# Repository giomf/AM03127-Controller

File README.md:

# AM03127 LED Panel Controller

This project provides a controller for AM03127 LED panels using an ESP32-C3 microcontroller. It communicates with the panel via RS232 and exposes a REST API through an HTTP server, along with a web interface for easy control.

## Features

- Control AM03127 LED panels via RS232 communication
- Display text with various animations and effects
- Create and manage schedules for automated content display
- Set and display the panel's internal clock
- RESTful API for programmatic control
- Web interface for easy management and OTA updates

## Hardware Requirements

- ESP32-C3 microcontroller
- AM03127 LED panel
- RS232 interface between ESP32-C3 and LED panel

## PCB Design

A custom PCB has been designed for this project. All PCB-related files, including schematics, board layouts, and manufacturing files, can be found in the [PCB](PCB/) folder.

## Software Architecture

The project is built with Rust and uses the following components:

- **Embassy**: Async runtime for embedded systems
- **ESP-HAL**: Hardware abstraction layer for ESP32 devices
- **PicoServe**: Lightweight HTTP server for embedded systems
- **Heapless**: Collections that don't require dynamic memory allocation

## Programs

The repository is a Cargo workspace plus the firmware, which is built separately for the ESP32-C3.

| Directory | What it is |
|---|---|
| [`am03127-firmware`](am03127-firmware/) | Firmware for the ESP32-C3: drives the panel over RS232, stores pages and schedules in flash, serves the REST API and the web UI, accepts OTA updates. |
| [`am03127-webui`](am03127-webui/) | Web UI written in Rust with [Leptos](https://leptos.dev) (WebAssembly). Edit pages and schedules, sync the clock, upload firmware. |
| [`am03127-server`](am03127-server/) | Server that consolidates all panels into one web UI and forwards each panel's API. |
| [`am03127-cli`](am03127-cli/) | Command line tool to control several panels at once. |
| [`am03127-client`](am03127-client/) | Shared HTTP client for the panel API and the `panel-config.toml` parser. Used by the CLI, the web UI and the server. |
| [`am03127-commands`](am03127-commands/) | Shared `no_std` models (pages, schedules, clock) and their AM03127 command encoding. Used by the firmware and everything else. |

### Firmware

The firmware connects to Wi-Fi, restores the stored pages and schedules on the panel and serves the API on port 80. The Wi-Fi credentials are compiled in:

```sh
export WIFI_SSID="MyNetwork" WIFI_PASS="secret"
just webui-firmware                     # build the web UI the firmware embeds
cd am03127-firmware && cargo run --release   # flash over USB (also writes the partition table)
```

For updates over Wi-Fi, `just save-image` builds the web UI and the release firmware into `firmware.bin`, and `just ota <panel-ip>` uploads it. The web UI's Device tab can upload it as well.

`GET /status` reports the build and the controller's health, shown in the web UI and by `am03127-cli status`:

- `version`: short git hash of the build, `-dirty` if the tree had uncommitted changes
- `uptime_secs`, `rssi` (Wi-Fi dBm), `heap_free` / `heap_used` (bytes)
- `panel_ok`: whether the panel answered the last command (`null` before the first one)

### Web UI

One Leptos crate, built in two variants:

- **Device** (default): served by the firmware for the panel it runs on.
- **Server** (`--features server`): shows a bar with all panels and their status; click a panel to edit it.

Both share the same tables and Device tab. Pages and schedules are edited in place; the last row of each table adds a new entry.

### Server

`am03127-server` serves the server variant of the web UI and forwards `/api/panel/<name>/…` to the panel's API, so the browser only talks to the server and the panels need no CORS.

```sh
am03127-server --config panel-config.toml --listen 0.0.0.0:8080 --web-root <built web UI>
```

`GET /api/panels` lists the configured panels.

### CLI

`am03127-cli` works on all (non-hidden) panels of `panel-config.toml`, or on the ones given with `--panels`:

```sh
am03127-cli status                                   # reachability, firmware version and health of each panel
am03127-cli info firmware.bin                        # build info of a firmware file
am03127-cli clock                                    # set the clocks to the local time
am03127-cli page A "Hello" --leading scroll_left     # send page A
am03127-cli schedule A A --from 2026-12-24 --to 2026-12-26   # show page A in that window
am03127-cli update firmware.bin --panels Kitchen     # OTA update one panel
am03127-cli --help                                   # all commands and options
```

### Panel configuration

The CLI and the server read the panels from a `panel-config.toml`:

```toml
[[panels]]
name = "Kitchen"
address = "192.168.1.23"   # host name or IP of the panel
floor = "Obergeschoss"     # optional, groups the panels in the server's web UI
model = "long"             # optional: "long" or "color"; omit for a standard panel

[[panels]]
name = "Spare"
address = "LED-8E-84.lan"
hidden = true              # skipped unless named with --panels
```

## Nix

The flake provides:

- Packages: `am03127-cli` (default), `am03127-server`, `am03127-webui` (server variant, built).
- NixOS modules:
  - `am03127-server`: runs the server with the web UI (`configFile`, `address`, `port`, `openFirewall`).
  - `am03127-clock`: syncs the panel clocks on a systemd timer.
  - `am03127-wednesday-schedule`: programs a weekly schedule slot.
- A dev shell with the toolchain, Trunk, espflash and just.

```nix
services.am03127-server = {
  enable = true;
  configFile = ./panel-config.toml;
  port = 80;
  openFirewall = true;
};
```

## Development

| Recipe | What it does |
|---|---|
| `just webui` | Web UI (device variant) with live reload against a mock panel (`am03127-webui/mock.py`). |
| `just webui-server` | Web UI (server variant) with `am03127-server` and two mock panels. |
| `just webui-firmware` | Builds the gzipped web UI the firmware embeds. |
| `just save-image` | Builds web UI and release firmware into `firmware.bin`. |
| `just ota <ip>` | Uploads `firmware.bin` to a panel. |

Both web UI recipes serve on <http://127.0.0.1:8080/>.

## API Documentation

The REST API documentation is available as [OpenAPI Specification](docs/openapi.yaml)

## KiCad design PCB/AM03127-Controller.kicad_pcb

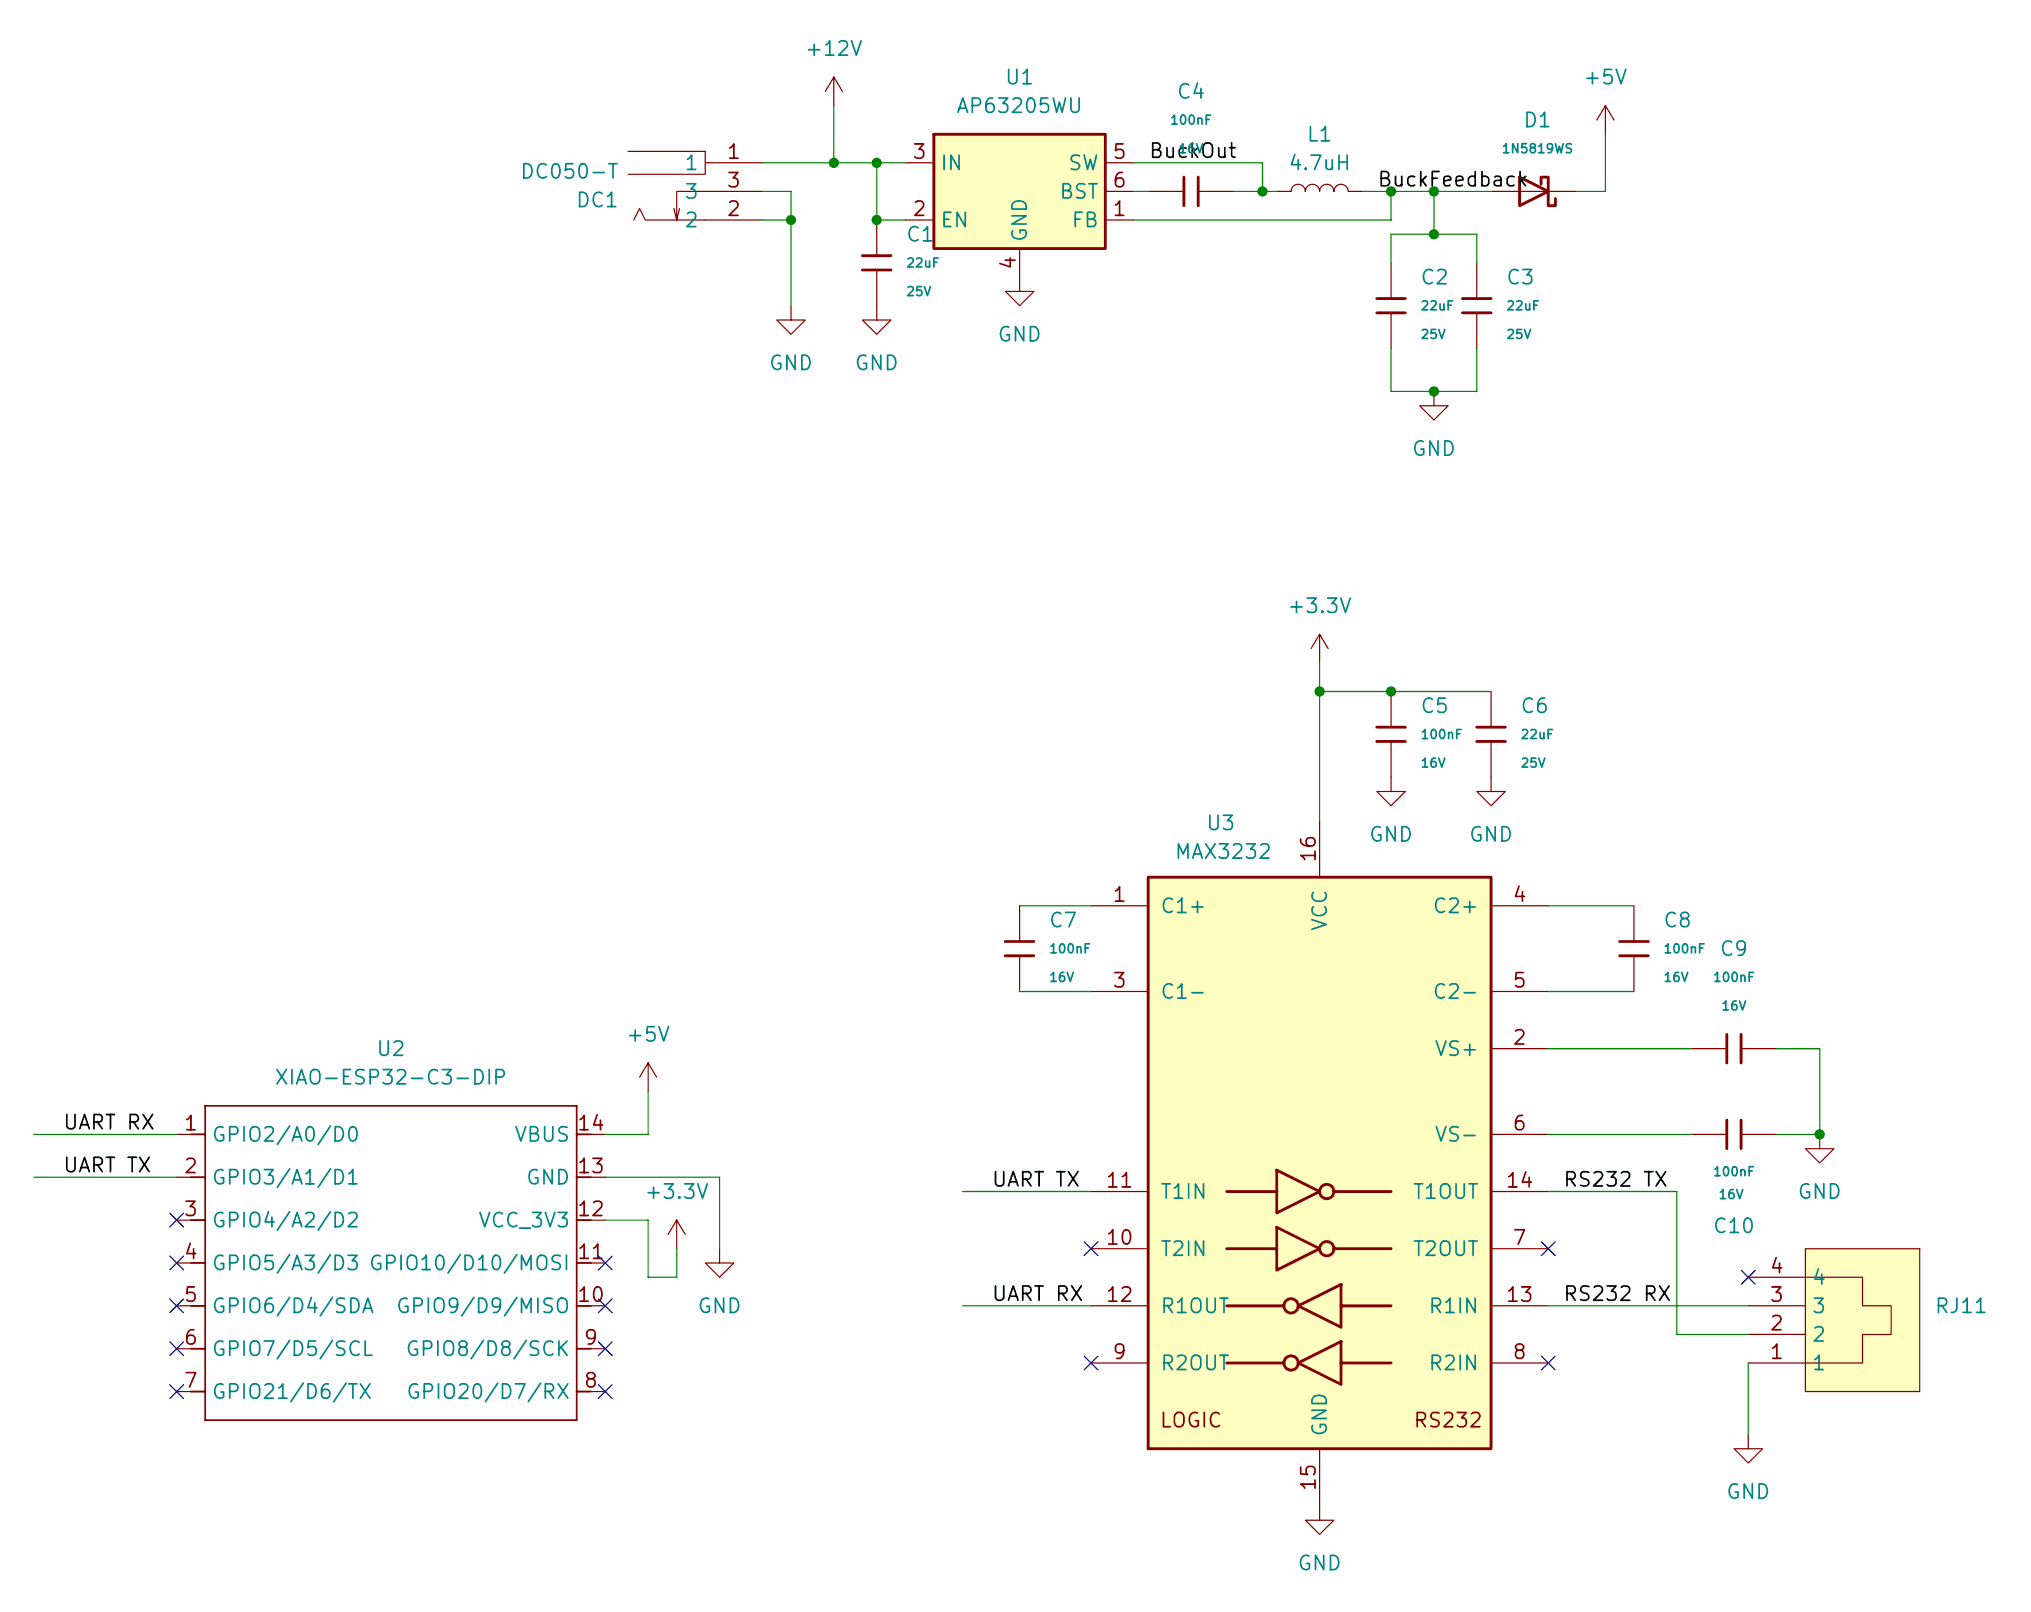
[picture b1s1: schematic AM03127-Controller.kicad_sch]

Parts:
C1, C2, C3, C6: 22uF; C_1206; Voltage Rated 25V; Tolerance ±10%; Part CL31A226KAHNNNE; LCSC C12891
C4, C5, C7, C8, C9, C10: 100nF; C_0402; Voltage Rated 16V; Tolerance ±10%; Part CL05B104KO5NNNC; LCSC C1525
D1: 1N5819WS; D_SOD-323; Forward Voltage (Vf@If) 600mV@1A; Reverse Voltage (Vr) 40V; Part 1N5819WS; LCSC C191023
DC1: DC050-T; DC-IN_DC050-T; LCSC Part C431534
L1: 4.7uH; L_1008_2520Metric
RJ11: PCB-6P4C-90_C189746; RJ11-TH_PCB-6P4C-90_C189746; LCSC Part C189746
U1: AP63205WU; TSOT-23-6
U2: XIAO-ESP32-C3-DIP; XIAO-ESP32C3-DIP
U3: MAX3232; SOIC-16_3.9x9.9mm_P1.27mm

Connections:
+3.3V: C5.1, C6.1, U2.12 (VCC_3V3), U3.16 (VCC)
+5V: D1.1, U2.14 (VBUS)
+12V: C1.1, DC1.1, U1.2 (EN), U1.3 (IN)
/BuckFeedback: C2.1, C3.1, D1.2, L1.2, U1.1 (FB)
/BuckOut: C4.2, L1.1, U1.5 (SW)
/RS232 RX: RJ11.3, U3.13 (R1IN)
/RS232 TX: RJ11.2, U3.14 (T1OUT)
/UART RX: U2.1 (GPIO2/A0/D0), U3.12 (R1OUT)
/UART TX: U2.2 (GPIO3/A1/D1), U3.11 (T1IN)
GND: C1.2, C2.2, C3.2, C5.2, C6.2, C9.2, C10.2, DC1.2, DC1.3, RJ11.1, U1.4 (GND), U2.13 (GND), U3.15 (GND)
unnamed: C4.1, U1.6 (BST)
unnamed: C7.1, U3.1 (C1+)
unnamed: C7.2, U3.3 (C1-)
unnamed: C8.1, U3.4 (C2+)
unnamed: C8.2, U3.5 (C2-)
unnamed: C9.1, U3.2 (VS+)
unnamed: C10.1, U3.6 (VS-)

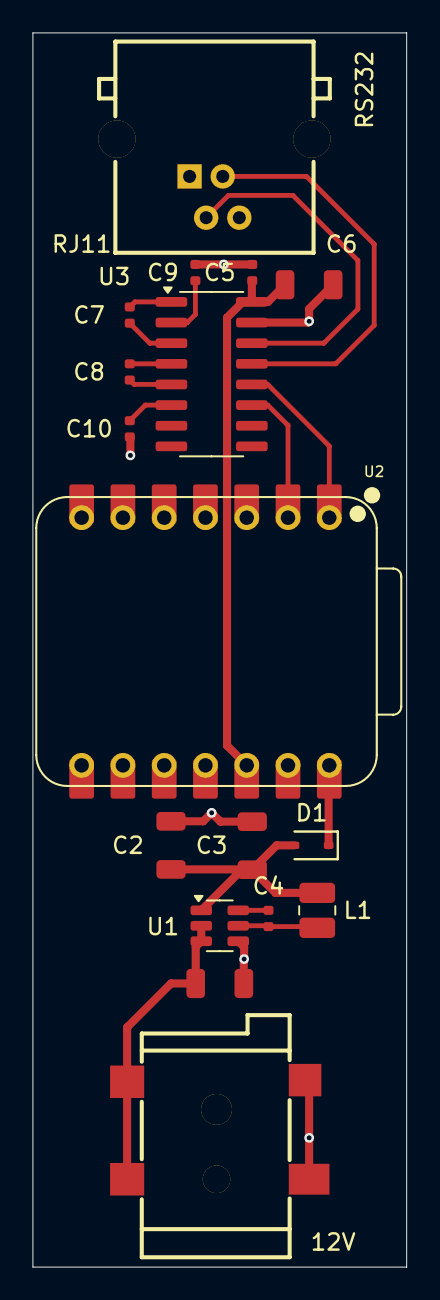
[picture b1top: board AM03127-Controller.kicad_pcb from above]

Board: 2 copper layers, 23.0 x 76.0 mm, 17 parts (0 on the bottom side), 17 nets.

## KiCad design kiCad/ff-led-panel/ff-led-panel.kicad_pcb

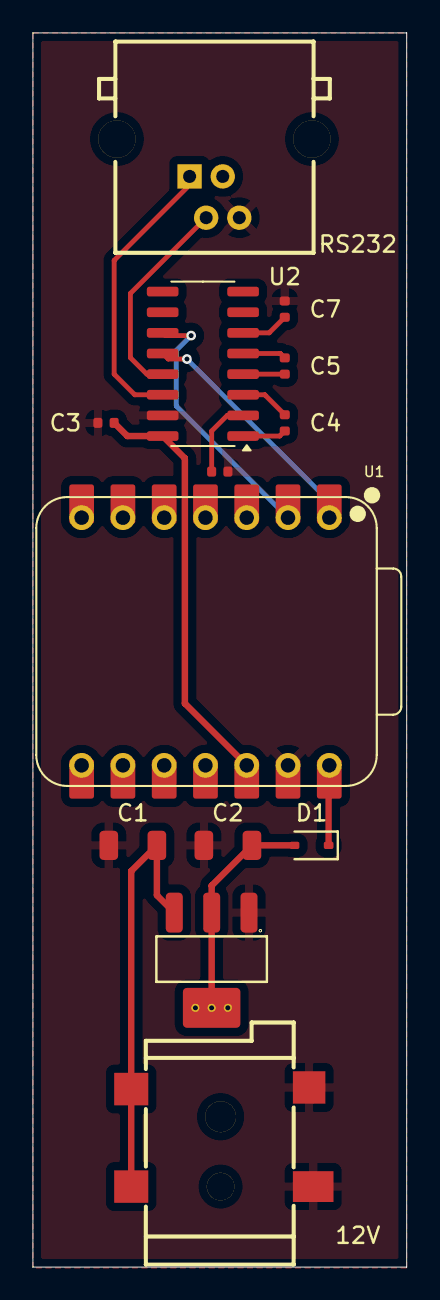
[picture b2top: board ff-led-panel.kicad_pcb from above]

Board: 2 copper layers, 23.0 x 76.0 mm, 13 parts (0 on the bottom side), 15 nets.

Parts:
12V: DC050-T; DC-IN_DC050-T
C1: 10uF; C_1206
C2: 22uF; C_1206
C3, C4, C5, C6, C7: 100nF; C_0402
D1: 1N5819WS; D_SOD-323
RS232: PCB-6P4C-90_C189746; RJ11-TH_PCB-6P4C-90_C189746
U1: XIAO-ESP32-C3-DIP; XIAO-ESP32C3-DIP
U2: MAX3232; SOIC-16_3.9x9.9mm_P1.27mm
U3: AMS1117; SOT-223_L6.5-W3.5-P2.30-LS7.0-BR

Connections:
/3.3V: C3.1, U1.12 (VCC_3V3), U2.16 (VCC)
/5V: C2.1, D1.2, U3.2 (VOUT), U3.4 (VOUT)
/5VD: D1.1, U1.14 (VBUS)
/12V: 12V.1, C1.1, U3.3 (VIN)
/RS232 RX: RS232.2, U2.13 (R1IN)
/RS232 TX: RS232.1, U2.14 (T1OUT)
/UART RX: U1.1 (GPIO2/A0/D0), U2.12 (R1OUT)
/UART TX: U1.2 (GPIO3/A1/D1), U2.11 (T1IN)
GND: 12V.2, 12V.3, C1.2, C2.2, C3.2, C6.2, C7.2, RS232.4, U1.13 (GND), U2.15 (GND), U3.1 (GND)
unnamed: C4.1, U2.1 (C1+)
unnamed: C4.2, U2.3 (C1-)
unnamed: C5.1, U2.4 (C2+)
unnamed: C5.2, U2.5 (C2-)
unnamed: C6.1, U2.2 (VS+)
unnamed: C7.1, U2.6 (VS-)

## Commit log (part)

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2025-03-31 init
2025-04-02 add picoserve hello world
2025-04-02 feat: Add AM03127 module with ID and command wrapping functions
2025-04-02 refactor: Replace format! with write! for no_std compatibility
2025-04-03 feat: Add page content module with display and formatting enums
2025-04-03 refactor: Convert page_content module to no_std with heapless::String
2025-04-03 feat: Add AM03127 module with page content and command wrapping functionality
2025-04-03 refactor: Add global string size constants and remove serde cfg flags
2025-04-03 refactor: Consolidate string size to single constant of 32
2025-04-03 feat: Add formatting module with Font, ColumnStart, and Clock enums
2025-04-03 style: Refactor formatting.rs to use core::fmt and consistent formatting
2025-04-03 Add am03127 library
2025-04-03 add uart
2025-04-08 Add webserver state
2025-04-13 Add uart write method
2025-04-13 Add clock endpoints
2025-04-13 Add text endpoint
2025-04-14 Add openapi documentation
2025-04-14 Add root endpoint servcing a static html
2025-04-14 Fix minor issues
2025-04-19 Add am03127 datasheat
2025-04-19 Init kicad project
2025-04-19 Add schedule endpoints
2025-04-20 Refactor AM03127 lib
2025-04-20 Add Schedule API
2025-04-20 Split server routes
2025-04-24 Add storage
2025-04-25 Add storage to server endpoints
2025-04-26 Add panel
2025-04-26 Add error handling
2025-04-28 Add schedule storage
2025-04-28 Add id validation for API endpoints
2025-04-28 Add pages GET endpoint
2025-04-28 Create own module for routers
2025-04-28 Add schedules GET endpoint
2025-04-28 Pass size for storage data buffer
2025-04-28 add init functions for wifi and network
2025-04-29 Fix wrong id validation
2025-05-05 Add custom error type
2025-05-05 Log errors for routers
2025-05-05 fix data buffer
2025-05-05 Review server config
2025-05-05 Remove println
2025-05-05 Extend response logging
2025-05-05 Review string lenghts
2025-05-14 Rename project
2025-05-14 Add pages and schedules post endpoints
2025-05-14 Renew openapi spec
2025-05-14 Add documentation
2025-05-14 Add Readme
2025-05-14 Remove DTOs
2025-05-14 Add reset endpoint
2025-05-14 Do not fail when uart gives negative response
2025-05-15 Optimize read_all from storage
2025-05-15 Remove uneeded build pattern from am03127 lib
2025-05-15 Set panel id in panel
2025-08-07 Add webpage into sources
2025-08-07 Update and sort esp-hal dependencies
2025-08-07 Update picoserve
2025-08-07 Update dependencies using cargo-edit
2025-08-07 Create gerbe files for pcb
2025-08-07 Restructure PCB project
2025-08-29 Refactor PCB to use global label nets
2025-08-30 Refactor LDO to Buckconverter
2025-09-06 Change Uart RX/TX
2025-09-11 Refactor PCB using buttom GND Plate
2025-09-27 Fix swaped pin for voltage regulator in PCB
2025-10-17 Update esp-hal
2025-10-23 Start implementing OTA
2025-10-28 Reconnect on wifi interrupts
2025-10-28 Use timeouts for uart read and write
2025-10-28 Add SNTP clock sync
2025-10-28 Initialize Panel on a seperate Task and allow it to fail
2025-10-28 Replace SharedPanel tuple struct with type alias
2025-10-30 Add OTA
2025-10-30 Update to esp-hal stable
2025-10-30 Add WaitingTime
2025-11-09 Update clock every 24h
2025-11-09 create workspace and split crates
2025-11-09 Add feature flag for sntp
2025-11-09 Remove unused traits
2025-11-09 Remove heapless and use esp alloc
2025-11-09 Add feature flag for web interface
2025-11-09 Configure rustfmt
2025-11-12 Remove unnesseary type alias
2025-11-12 Add offset for winter time
2025-11-12 Add delay before init panel
2025-11-12 Reduce heap size due to stack overflows
2025-11-12 Print current booted partition when starting
2025-11-12 Fix bug returning all items
2025-11-12 Update webinterface
2025-11-13 Fix a crash when ota chunk is not alligned
2025-12-09 Adapt documentation
2025-12-09 Adapt readme
2026-04-01 chore: Update picoserve to v0.18.0
2026-04-01 fix: potential bug when reading unaligned bytes in ota
2026-04-01 refactor: Refactor ota handler
2026-04-01 fix: Abort if read ota image fails
2026-04-01 fix: increase read request time for ota
2026-04-01 Add justfile for useful commands
2026-04-01 feat: reset system after successful ota update
2026-04-01 fix: recreate UDP socket for timing task every iteration
2026-04-01 feat: Add automatic date time saving switch for eu
2026-04-05 feat(cli): use indicatif to print progress bars
2026-04-05 feat(cli): init cli
2026-04-05 feat(cli): add status command
2026-04-05 feat(cli): Allow to specify panels in commands
2026-04-05 feat(cli): Add error handling via anyhow
2026-04-05 feat(cli): read config
2026-04-06 feat(cli): Add update command
2026-04-06 chore: Split up workspaces to allow multi target builds
2026-04-06 feat(ctrl): Add status endpoint
2026-04-06 feat(cli): Print status information from /status endpoint
2026-04-06 feat(ctrl): bake build time, date and version into firmware
2026-04-09 feat(cli): use colorful output in status
2026-04-09 feat(ctrl): Add partition information to boot header
2026-04-09 fix(ctrl): erase ota partition before writing image
2026-04-09 feat(cli): list available panels from config
2026-04-09 feat(cli): add open command
2026-04-09 feat(cli): Add cli list argument description
2026-04-09 feat(cli): print firmware infos before updating
2026-04-10 feat(cli): add info command
2026-04-10 fix(cli): use config only where its needed
2026-04-11 feat(cli): Streamline update output
2026-04-11 feat(ctrl): Print SSID in use
2026-04-11 feat(cli): Add clock command
2026-04-11 refactor(cli): Cut out am03127-client to allow future backend implementation to use the same lib
2026-04-11 feat(all): Rename workspace members
2026-04-11 feat(cli): indent command outputs
2026-04-11 feat(cli): Add page command
2026-04-11 chore(firmware): Remove unused partition-table
2026-05-23 feat: Add plain console output
2026-06-03 feat: reset european char table when init the panel
2026-06-03 feat: Add systemd timer to push clock every 12h
2026-06-03 feat: build cli via nix
2026-06-03 feat: Add hidden argument for panel config
2026-06-03 feat: disactivate sntp feature
2026-06-03 feat(cli): add schedule
2026-06-03 chore: fix linked projects
2026-06-03 style: format all files
2026-06-04 feat: Add wednesday schedule nixos module
